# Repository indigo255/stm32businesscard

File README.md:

# Quick overview
I made a buisness card that uses an STM32 to allow exploration of a modified mandelbrot fractal. It has the following features:
* Rechargable via USB-C with NiMH AAA batteries
* 160x80 colored display
* Custom bordertracing algorithm to accelerate use
* Custom modification of mandelbrot for pretty pictures

# Code
I used STM32's HAL to speed up development, which has unfortunately left the project a mess. The source files are [here](program/stm32f1_buisnesscard_v1/Core/Src) and header files [here](program/stm32f1_buisnesscard_v1/Core/Inc).

# Writeup
## Computing the Mandelbrot Set
The mandelbrot set is a famous two-dimensional fractal known for its infinite complexity. Zooming past the famous bulbs, you’re bound to find some extremely beautiful patterns if you process and color the data right. One thing that always interested me about the set is the simplicity of how the fractal is rendered. It’s spooky how basic logic can create such complex patterns that will forever be explored by mathematicians. For this reason, graphing the mandelbrot set has always been my version of a “hello world”- a quick cool program I write when testing new languages, environments, etc. I’ve implemented the fractal at least a dozen times. 

Reading the wikipedia page is a good resource for understanding the mandelbrot fractal. In short, pixels on the screen are translated to complex numbers which are fed into a simple formula up to 255 times. If that number raises above a certain magnitude, the pixel is shaded based on iteration count and the next pixel is processed. Pixels that have a higher iteration count take longer to process.

I wanted my business card to allow users to explore the set with little to no wait time. I also wanted to allow people to zoom in pretty far so they’d never run out of new patterns to explore, requiring relatively high precision. Achieving this was more difficult than I anticipated due to the nature of the STM32F103. 

The STM32F103 has strengths and weaknesses. It boasts a Arm Cortex M3 that can be clocked up to 72MHz (I ran at 62MHz using the internal oscillator). There’s single cycle 32 bit hardware multiplication. Memory access is instantaneous and only takes a single cycle. With the MCU being on the lower end of the STM32 lineup, there’s also drawbacks. There’s no FPU; all operations to floats would have to be done in software. The MCU also has 20 KB of RAM, not even enough to hold a full framebuffer for my tiny display. 
With no optimizations, the mandelbrot set took a few minutes to render on a 160x80 display. While waiting for my PCBs to arrive, I took a devkit I had on hand and started optimizing to chip down the time. 

## Fixed Point Arithmetic
We lack an FPU. The compiler needs to implement expensive operations to handle floats in software, slowing render times to hours. To work around our lack of FPU, I used fixed point arithmetic, which also takes advantage of our single cycle multiplication time. The position of the decimal is hardcoded. Integers are simply shifted to the left by n bits, and bits before point n are considered the decimal. Multiplication is carried out as per usual, but the result will be scaled by 2^n. So, after multiplication, we shift the result n bits to the right to scale it back. To prevent overflows during multiplication, I ended up multiplying with 64 bit integers, which was still much faster than float multiplication. 

While experimenting with decimal placement, I shifted the decimal too much to the left. I haven’t taken the time to fully understand how, but this introduced some really aesthetically pleasing bugs. I don’t fully comprehend why the bands form. Because numbers get clipped above a certain threshold, this decimal placement also creates copies of the mandelbrot set scattered throughout the complex plane in a way I think is really fun to explore. 

At this point, the set rendered nearly instantaneously in locations that didn’t include the black blobs of the set. Render time from decreased from minutes to a few seconds.

## Color
Color for each iteration count is computed beforehand to generate a lookup table for each iteration. This is faster than computing on the fly, as the STM32F1 has single cycle memory access time.

I didn’t use the green channel, originally for aesthetic purposes. Later, as described in border tracing, I needed to store which pixels were rendered, and whether or not they were in the mandelbrot set. With my framebuffer and color lookup table, there was only about 500B of memory left, so I ended up using the green channel to store information. Using the green channel gave me a convenient way to access data on each pixel, and a conveniently visual way to debug.

## Framebuffer
There’s a lot of overhead to sending each pixel individually. The LCD controller requires coordinates for each drawing command, not to mention overhead of the SPI headers. The obvious solution is to keep a framebuffer and to send all data in one command. Due to limited memory, the framebuffer only contains half the screen; each half is rendered separately. Additionally, when panning the view, the framebuffer is simply shifted to avoid re-rendering parts already on the screen.

## Border Tracing
The mandelbrot set is full; if a closed edge can be found, everything inside has the same number of iterations. This property can be exploited to dramatically decrease render times by searching for closed loops throughout the set. Because of the bugs introduced by fixed point arithmetic, I found this property to only remain true for points inside the set- points that require 255 iterations. Despite just appearing black, these points often take a majority of the compute time, especially when zoomed out.

I decided to take a shot at border tracing myself. At this point, I had assembled my first working PCB, but developing and debugging the algorithm would be much easier on a computer. I quickly rewrote the code to work on my desktop using Raylib so I could debug faster- the STM32F1 contains only a few hardware breakpoints, and lacks the ability to set watchpoints.

The very basic principle of border detection is simple: when you run across a black pixel, go to the next pixel that is black but touching a colored pixel. While doing this, never backtrack. When you come across where you started, the curve is closed, and you can then shade the inside. There’s a few inherent problems to this- the largest is that we’re taking discrete samples of a fractal, where edges are infinitely complex. Very fine detail can make a curve look closed, when in reality there’s a sliver that’s just not visible due to sample resolution. Take below as an example. There’s blue spots enclosed within the edge.

 <br>

One of the issues this can cause is that there’s points where the algorithm sees two edges. Sometimes, the algorithm can corner itself as seen below. The obvious solution is to keep a list of points where there’s two possible paths; when the algorithm traps itself, it can pop off the most recent location and keep running.

I got border tracing working by tracking pixel locations with multiple detectable edges. I spent a lot of time (days of actual working) avoiding this solution, as there was no way I could prove the list of pixels with multiple edges wouldn’t overflow, and the algorithm *could* fail. Overflowing the array was literally never an issue, and the array only holds 32 potential locations.

To prevent pixels from being re-rendered, I stored information in the green channel of the image. My images never used green anyway, and I wouldn’t have to eat any more memory (I only had ~500 bytes left). Using the green channel also gave me a conveniently visual way to debug.

## Border Tracing in Action
https://github.com/user-attachments/assets/f47e8c3c-38c0-41ec-97d2-28774dae4d73

## Benchmarking Border Tracing Performance
I wrote a GDB script to benchmark performance with and without border tracing. Results improved up to 75%. I was planning on including a table and images here, but I'm running out of time writing this article. I will likely add it later!  

## Hardware Design
Hardware was relatively straight forward. Every iteration fit on a 2 layer PCB. I miscalculated how much power was consumed by a power of 10- so my first PCB used non-rechargeable zinc-ion batteries, as this was the cheapest solution I could find. My first card worked without issues, as the only real circuitry was debouncing and a step-down switching regulator.

After discovering my error, I decided to make a more complex design that allowed recharging via USB-C for AAA batteries. To maximize battery longevity, a switching regulator was used for the step-up (battery) supply, while a simple linear regulator for USB-C. To avoid the batteries from discharging, I put a voltage supervisor to shut down the switching regulator at 1V. The switching regulator has true shutdown- blocking inputs when shut off. The voltage monitor uses a capacitor to time how long it should wait until turning back on above 1V. While finishing up the PCB I was tired and didn’t care to calculate this value, so I just slapped a 1uF cap down- hence the card takes around 5 seconds to become powered after a battery is inserted. Two ideal diode ICs are used for supply ORing so the supplies aren't in conflict while charging. 

My second iteration worked almost flawlessly. If it was unplugged while charging, however, I’d start running into issues. The USB bus was at 3v for some reason, powering components that should have been off. I found the ideal diode IC I was using as a power ORing circuit was latching on. Despite the name, "ideal diode" ICs don’t actually block current flowing from output to input. The power would travel through the linear regulator, powering the nmos that enabled the ideal diode IC. This was fixed by simply adding a diode, as circled in magenta. I was able to fit the diode on the PCB via hand-made modifications.

In the photo above, bat_3v was the power rail of the battery voltage regulator. Obviously, when the nmos is active, the signal won’t drop to 0v as intended- the diode should be replaced with a resistor, and the 10k resistor should be replaced with a short. So I didn’t have to order new PCBs, I simply substituted a 0Ω for the 10kΩ, and made a messy solder bridge to fit a 10kΩ across the diode pads.

I misunderstood the datasheet for the display's backlight, and thought it had to be run at exactly 2.9-3.1V. This is why my whole card runs at 3v. In reality, it's just an LED with a forward voltage of 3V. Because we power the backlight at exactly the forward voltage, the backlight doesn't burn itself out. However, the voltage is briefly above the forward voltage while the switching regulator powers on- probably not great for longevity.
 
## Assembly
I used a hot air station to assemble the cards. The final PCBs were purchased a bit too close to the career fair, so a stencil would be very expensive to ship. To work around this, I just mixed my solder paste with flux. This was a mistake. While I get good results, each card takes a very long time to make. Maybe I was being too precise, but check out how many pads there are below. I was planning to hand them out at the fair, but I’m now only planning on handing them out during interviews. Additionally, getting the pins of the MCU to align properly and remove the solder bridges with wick was excruciating.

## How I feel about the end product
I think the card looks good. I like how the buttons feel, how the screen looks, and the overall design. I do wish the battery wasn't so chunky, but alas- NiMH AAAs are litteraly the cheapest rechargable batteries I could find (at sufficient power density). It would also be nice if I could have them assembled for me, so I could hand them out more freely. The border tracing algorithm worked pretty well, but wasn't quite fast enough when zoomed in, or where there's a lot of sharp edges. One of those locations is, unfortunately, where card starts on boot- a location I choose becuase it looks very good. If I were to redesign this, I'd go with a cheaper and higher spec MCU, preferebly one with an FPU. I chose an STM32 because I had a dev board, but they're really too expensive and low spec for a project such as this; I don't need to pay for automotive grade hardware.

I also swapped the "charging" and "full" text. I'm not fixing it.

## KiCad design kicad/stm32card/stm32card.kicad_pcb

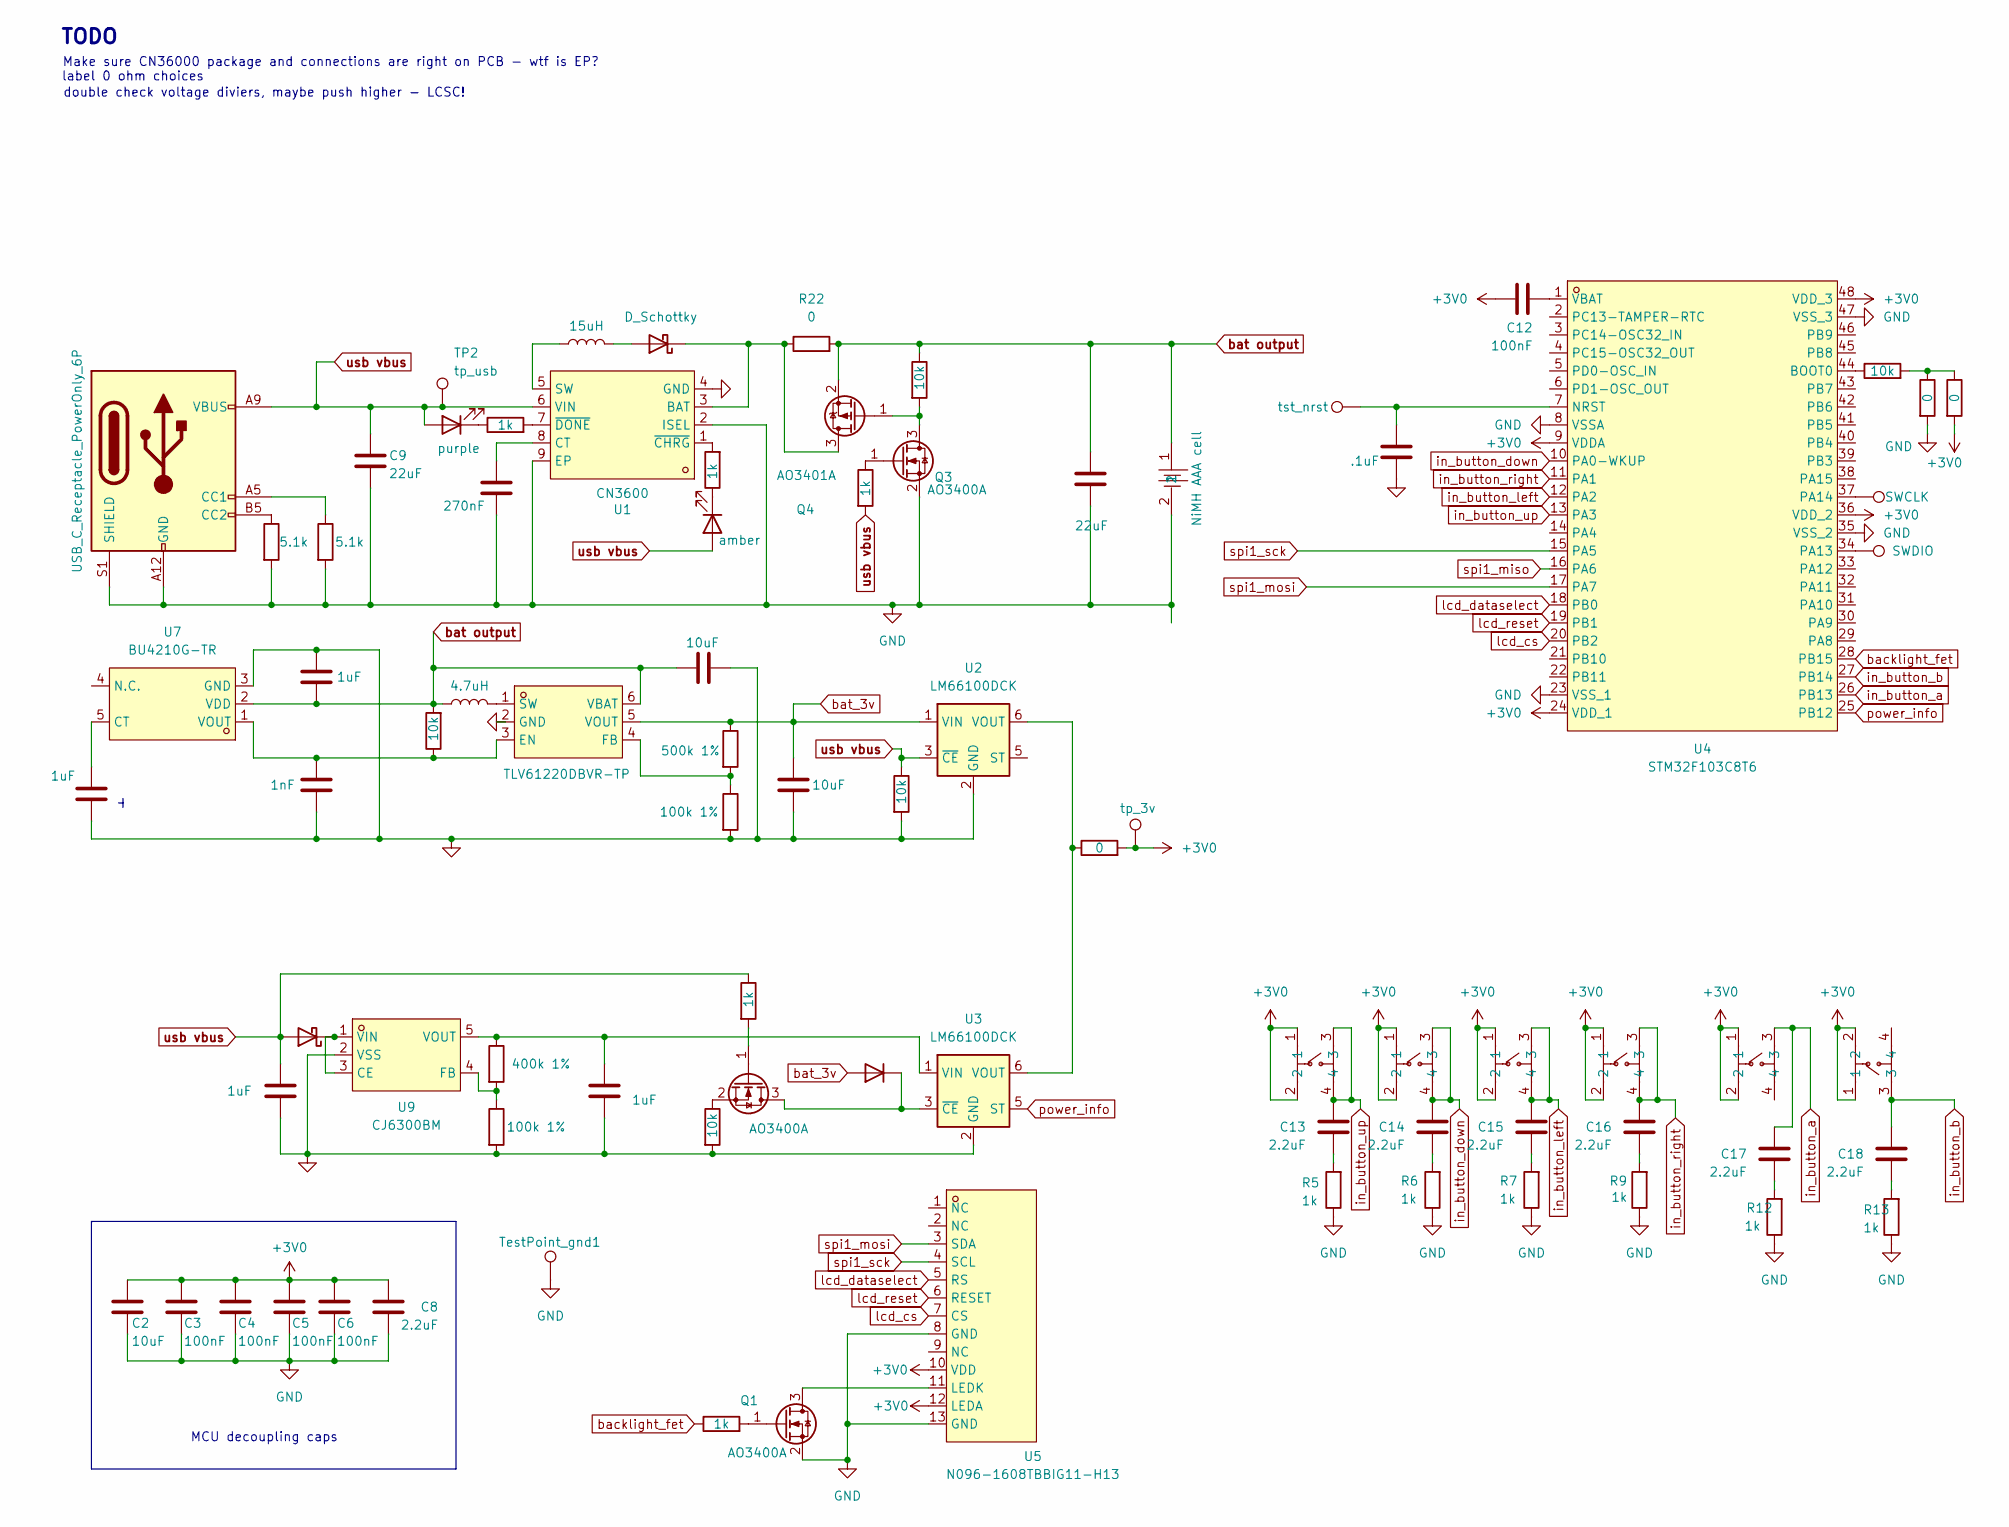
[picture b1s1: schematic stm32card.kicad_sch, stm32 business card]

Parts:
BT1: NiMH AAA cell; BAT-SMD_BH-AAA-B5BA021; LCSC Part C7525446
C1, C9: 22uF; C_0603_1608Metric
C2, C22, C25: 10uF; C_0603_1608Metric
C3, C4, C5, C6, C12: 100nF; C_0603_1608Metric
C7: 270nF; C_0805_2012Metric
C8, C13, C14, C15, C16, C17, C18: 2.2uF; C_0603_1608Metric
C10, C20, C21, C24: 1uF; C_0603_1608Metric
C11: .1uF; C_0603_1608Metric
C19: 1nF; C_0603_1608Metric
D1, D4: D_Schottky; D_SMA
D2: purple; LED_0805_2012Metric
D3: amber; LED_0603_1608Metric
D5: 1N4148; D_SOD-323
J1: USB_C_Receptacle_PowerOnly_6P; SAMESKY_UJC-H-G-SMT-2-P6-TR
L1: 15uH; IND-SMD_L7.2-W6.6_GPSR07X0
L2: 4.7uH; IND-SMD_L5.8-W5.2
Q1, Q2, Q3: AO3400A; SOT-23
Q4: AO3401A; SOT-23
R1, R2: 5.1k; R_0603_1608Metric
R3, R5, R6, R7, R9, R12, R13, R14, R15, R23, R26: 1k; R_0603_1608Metric
R4, R8, R20, R21, R25: 10k; R_0603_1608Metric
R10, R11, R22, R24: 0; R_0603_1608Metric
R16: 500k 1%; R_0603_1608Metric
R17, R19: 100k 1%; R_0603_1608Metric
R18: 400k 1%; R_0603_1608Metric
SWCLK1: SWCLK; TestPoint_Pad_D2.0mm
SWDIO1: SWDIO; TestPoint_Pad_D2.0mm
TP2: tp_usb; TestPoint_Pad_D2.0mm
TP3: tp_3v; TestPoint_Pad_D2.0mm
TestPoint_gnd1: tp_gnd; TestPoint_Pad_D2.0mm
U1: CN3600; ESOP-8_L4.9-W3.9-P1.27-LS6.0-BL-EP; LCSC Part C3034871
U2, U3: LM66100DCK; SOT-363_SC-70-6
U4: STM32F103C8T6; LQFP-48_L7.0-W7.0-P0.50-LS9.0-BL; LCSC Part C8734
U5: N096-1608TBBIG11-H13; OLED-SMD_ST7735S; LCSC Part C2890616
U6: TLV61220DBVR-TP; SOT-23-6_L2.9-W1.6-P0.95-LS2.8-BL; LCSC Part C47117507
U7: BU4210G-TR; SSOP-5_L2.9-W1.6-P0.95-LS2.8-TL; LCSC Part C2066584
U9: CJ6300BM; SOT-23-5_L2.9-W1.6-P0.95-LS2.8-BR; LCSC Part C2829398
b_a1: TSD003A04126A02; SW-SMD_4P-L6.0-W6.0-P4.50-LS8.6; LCSC Part C2888573
b_b1: TSD003A04126A02; SW-SMD_4P-L6.0-W6.0-P4.50-LS8.6; LCSC Part C2888573
b_down1: TSD003A04126A02; SW-SMD_4P-L6.0-W6.0-P4.50-LS8.6; LCSC Part C2888573
b_left1: TSD003A04126A02; SW-SMD_4P-L6.0-W6.0-P4.50-LS8.6; LCSC Part C2888573
b_right1: TSD003A04126A02; SW-SMD_4P-L6.0-W6.0-P4.50-LS8.6; LCSC Part C2888573
b_up1: TSD003A04126A02; SW-SMD_4P-L6.0-W6.0-P4.50-LS8.6; LCSC Part C2888573
tst_nrst1: tst_nrst; TestPoint_Pad_D2.0mm

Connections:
+3V0: C2.1, C3.1, C4.1, C5.1, C6.1, C8.2, C12.1, R10.2, R24.2, TP3.1, U4.9 (VDDA), U4.24 (VDD_1), U4.36 (VDD_2), U4.48 (VDD_3), U5.10 (VDD), U5.12 (LEDA), b_a1.1, b_a1.2, b_b1.1, b_b1.2, b_down1.1, b_down1.2, b_left1.1, b_left1.2, b_right1.1, b_right1.2, b_up1.1, b_up1.2
GND: BT1.2, C1.2, C2.2, C3.2, C4.2, C5.2, C6.2, C7.2, C8.1, C9.2, C10.2, C11.2, C19.2, C20.1, C21.2, C22.2, C24.2, C25.2, J1.A12 (GND), J1.B12 (GND), J1.S1 (SHIELD), J1.SH1, J1.SH2, J1.SH3, J1.SH4, Q1.2 (S), Q3.2 (S), R1.2, R2.2, R4.2, R5.1, R6.1, R7.1, R9.1, R11.2, R12.1, R13.1, R17.2, R19.2, R21.2, TestPoint_gnd1.1, U1.2 (ISEL), U1.4 (GND), U1.9 (EP), U2.2 (GND), U3.2 (GND), U4.8 (VSSA), U4.23 (VSS_1), U4.35 (VSS_2), U4.47 (VSS_3), U5.8 (GND), U5.13 (GND), U6.2 (GND), U7.3 (GND), U9.2 (VSS)
unnamed: C13.1, R5.2
unnamed: C14.1, R6.2
unnamed: C15.1, R7.2
unnamed: C16.1, R9.2
unnamed: C17.1, R12.2
unnamed: C18.1, R13.2
unnamed: D1.2 (A), L1.2
unnamed: D1.1 (K), Q4.3 (D), R22.1, U1.3 (BAT)
unnamed: D2.1 (K), R14.1
unnamed: D3.1 (K), R15.1
unnamed: D4.1 (K), U9.1 (VIN), U9.3 (CE)
unnamed: D5.1 (K), Q2.3 (D), U3.3 (~CE)
unnamed: J1.A5 (CC1), R2.1
unnamed: J1.B5 (CC2), R1.1
unnamed: Q1.3 (D), U5.11 (LEDK)
unnamed: Q1.1 (G), R26.2
unnamed: Q2.1 (G), R23.2
unnamed: Q2.2 (S), R21.1
unnamed: Q3.3 (D), Q4.1 (G), R25.2
unnamed: Q3.1 (G), R3.1
unnamed: R8.2, R10.1, R11.1
unnamed: C7.1, U1.8 (CT)
unnamed: L1.1, U1.5 (SW)
unnamed: R15.2, U1.1 (~CHRG)
unnamed: R14.2, U1.7 (~DONE)
unnamed: R24.1, U2.6 (VOUT), U3.6 (VOUT)
unnamed: C24.1, R18.1, U3.1 (VIN), U9.5 (VOUT)
unnamed: R8.1, U4.44 (BOOT0)
unnamed: C11.1, U4.7 (NRST), tst_nrst1.1
unnamed: SWDIO1.1, U4.34 (PA13)
unnamed: SWCLK1.1, U4.37 (PA14)
unnamed: C12.2, U4.1 (VBAT)
unnamed: C19.1, R20.1, U6.3 (EN), U7.1 (VOUT)
unnamed: R16.2, R17.1, U6.4 (FB)
unnamed: L2.2, U6.1 (SW)
unnamed: C10.1, U7.5 (CT)
unnamed: R18.2, R19.1, U9.4 (FB)
backlight_fet: R26.1, U4.28 (PB15)
bat output: BT1.1, C1.1, C20.2, C25.1, L2.1, Q4.2 (S), R20.2, R22.2, R25.1, U6.6 (VBAT), U7.2 (VDD)
bat_3v: C22.1, D5.2 (A), R16.1, U2.1 (VIN), U6.5 (VOUT)
in_button_a: C17.2, U4.26 (PB13), b_a1.3
in_button_b: C18.2, U4.27 (PB14), b_b1.3
in_button_down: C14.2, U4.10 (PA0-WKUP), b_down1.3, b_down1.4
in_button_left: C15.2, U4.12 (PA2), b_left1.3, b_left1.4
in_button_right: C16.2, U4.11 (PA1), b_right1.3, b_right1.4
in_button_up: C13.2, U4.13 (PA3), b_up1.3, b_up1.4
lcd_cs: U4.20 (PB2), U5.7 (CS)
lcd_dataselect: U4.18 (PB0), U5.5 (RS)
lcd_reset: U4.19 (PB1), U5.6 (RESET)
power_info: U3.5 (ST), U4.25 (PB12)
spi1_miso: U4.16 (PA6)
spi1_mosi: U4.17 (PA7), U5.3 (SDA)
spi1_sck: U4.15 (PA5), U5.4 (SCL)
usb vbus: C9.1, C21.1, D2.2 (A), D3.2 (A), D4.2 (A), J1.A9 (VBUS), J1.B9 (VBUS), R3.2, R4.1, R23.1, TP2.1, U1.6 (VIN), U2.3 (~CE)

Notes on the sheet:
Make sure CN36000 package and connections are right on PCB - wtf is EP?
MCU decoupling caps
label 0 ohm choices
double check voltage diviers, maybe push higher - LCSC!
TODO

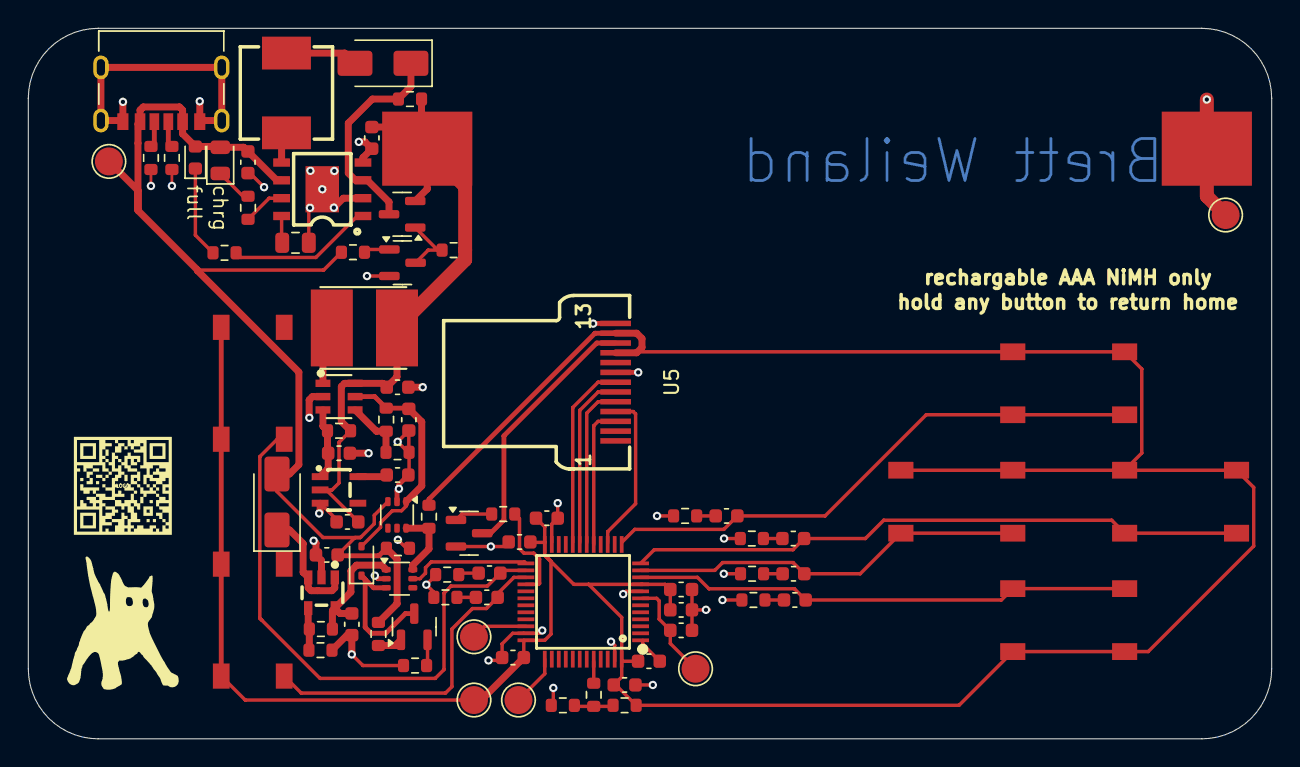
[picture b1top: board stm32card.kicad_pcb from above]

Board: 2 copper layers, 88.9 x 50.8 mm, 83 parts (0 on the bottom side), 55 nets.

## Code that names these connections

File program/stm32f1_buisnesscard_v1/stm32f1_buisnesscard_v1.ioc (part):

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Mcu.Name=STM32F103C(8-B)Tx
Mcu.Package=LQFP48
Mcu.UserName=STM32F103C8Tx
PA0-WKUP.GPIOParameters=GPIO_PuPd
PA0-WKUP.GPIO_PuPd=GPIO_PULLDOWN
PA0-WKUP.Signal=GPXTI0
PA1.GPIOParameters=GPIO_PuPd
PA1.GPIO_PuPd=GPIO_PULLDOWN
PA1.Signal=GPXTI1
PA13.Mode=Serial_Wire
PA13.Signal=SYS_JTMS-SWDIO
PA14.Mode=Serial_Wire
PA14.Signal=SYS_JTCK-SWCLK
PA2.GPIOParameters=GPIO_PuPd
PA2.GPIO_PuPd=GPIO_PULLDOWN
PA2.Signal=GPXTI2
PA3.GPIOParameters=GPIO_PuPd
PA3.GPIO_PuPd=GPIO_PULLDOWN
PA3.Signal=GPXTI3
PA5.Mode=TX_Only_Simplex_Unidirect_Master
PA5.Signal=SPI1_SCK
PA7.Mode=TX_Only_Simplex_Unidirect_Master
PA7.Signal=SPI1_MOSI
PB0.GPIOParameters=GPIO_Speed,GPIO_PuPd
PB0.GPIO_PuPd=GPIO_NOPULL
PB0.GPIO_Speed=GPIO_SPEED_FREQ_HIGH
PB0.Signal=GPIO_Output
PB1.GPIOParameters=GPIO_Speed
PB1.GPIO_Speed=GPIO_SPEED_FREQ_HIGH
PB1.Signal=GPIO_Output
PB12.GPIOParameters=GPIO_PuPd
PB12.GPIO_PuPd=GPIO_PULLUP
PB12.Signal=GPXTI12
PB13.GPIOParameters=GPIO_PuPd
PB13.GPIO_PuPd=GPIO_PULLDOWN
PB13.Signal=GPXTI13
PB14.GPIOParameters=GPIO_PuPd
PB14.GPIO_PuPd=GPIO_PULLDOWN
PB14.Signal=GPXTI14
PB15.GPIOParameters=PinState,GPIO_PuPd,GPIO_ModeDefaultOutputPP
PB15.GPIO_ModeDefaultOutputPP=GPIO_MODE_OUTPUT_PP
PB15.GPIO_PuPd=GPIO_NOPULL
PB15.PinState=GPIO_PIN_SET
PB15.Signal=GPIO_Output
PB2.GPIOParameters=GPIO_Speed
PB2.GPIO_Speed=GPIO_SPEED_FREQ_HIGH
PB2.Signal=GPIO_Output
RCC.SYSCLKFreq_VALUE=64000000
RCC.SYSCLKSource=RCC_SYSCLKSOURCE_PLLCLK
board=custom

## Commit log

2025-02-13 init
2025-02-13 fixing readme
2025-03-24 rev1a
2025-03-24 added preview
2025-03-30 begin fixed point integer test
2025-03-30 readme image
2025-03-31 finished basic screen test, aboutta start converting to fixed point
2025-03-31 fixed point arithmatic done
2025-04-02 colorschemes developed, fixed point arithmatic fixed
2025-04-30 applying 4 more jobs
2025-04-30 readme
2025-04-30 readme, submodule fix
2025-05-11 optimized spi
2025-06-05 about to add border tracing, thick in the weeds
2025-07-13 need to organize, redid PCB
2025-09-03 quick update for garmin
2025-09-03 Update README.md
    temp readme
2025-09-03 temp images
2025-09-03 quick update for garmin day
2025-09-23 pre-readme
2025-09-23 pre readme
2025-09-23 readme no images, videos or comparisons
2025-09-23 added images
2025-09-23 converted vid to mp4
2025-09-23 more readme imgs
2025-09-23 readme done
2025-09-23 lil change
2025-09-23 cleaning
2025-09-23 Update README.md
    last lil change
2025-09-23 trying to fix video
2025-10-01 spelling mistake
    spelling mistake
2026-02-24 Update README.md
    updated some writing
2026-02-24 fixed video
